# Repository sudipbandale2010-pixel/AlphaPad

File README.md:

# AlphaPad
It is a unique Macropad with unique features, it includes 9 keys and an Oled screen.

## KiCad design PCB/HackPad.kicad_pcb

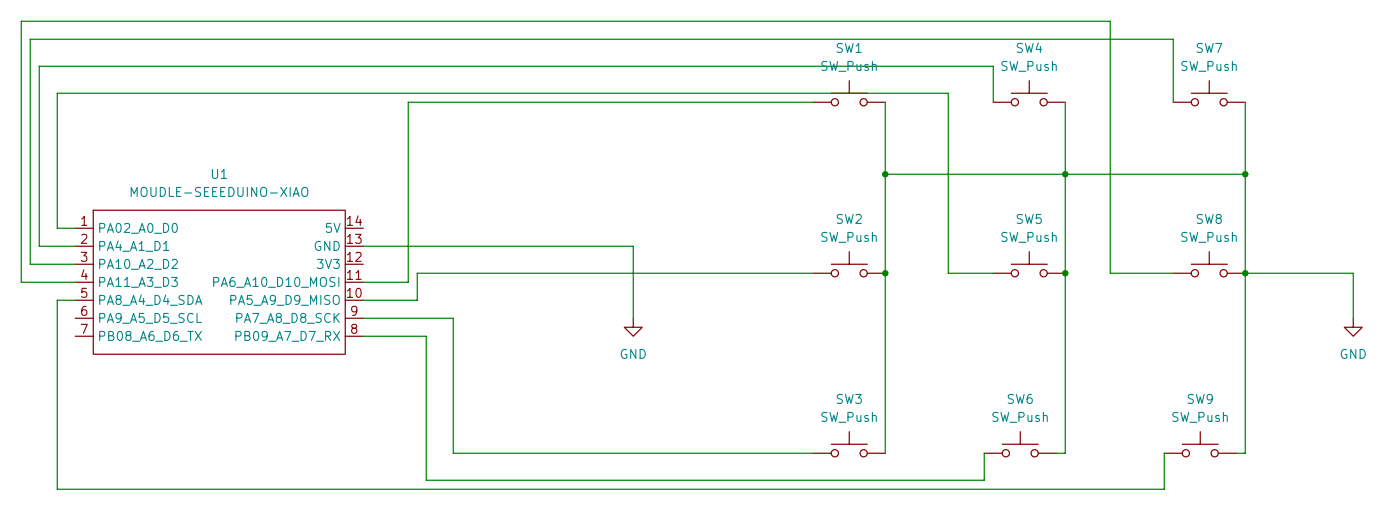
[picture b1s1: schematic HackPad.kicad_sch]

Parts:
SW1, SW2, SW3, SW4, SW5, SW6, SW7, SW8, SW9: SW_Push; SW_Cherry_MX_1.00u_PCB
U1: MOUDLE-SEEEDUINO-XIAO; XIAO-Generic-Hybrid-14P-2.54-21X17.8MM

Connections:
GND: SW1.2, SW2.2, SW3.2, SW4.2, SW5.2, SW6.2, SW7.2, SW8.2, SW9.2, U1.13 (GND)
unnamed: SW5.1, U1.1 (PA02_A0_D0)
unnamed: SW4.1, U1.2 (PA4_A1_D1)
unnamed: SW2.1, U1.10 (PA5_A9_D9_MISO)
unnamed: SW1.1, U1.11 (PA6_A10_D10_MOSI)
unnamed: SW3.1, U1.9 (PA7_A8_D8_SCK)
unnamed: SW9.1, U1.5 (PA8_A4_D4_SDA)
unnamed: SW7.1, U1.3 (PA10_A2_D2)
unnamed: SW8.1, U1.4 (PA11_A3_D3)
unnamed: SW6.1, U1.8 (PB09_A7_D7_RX)

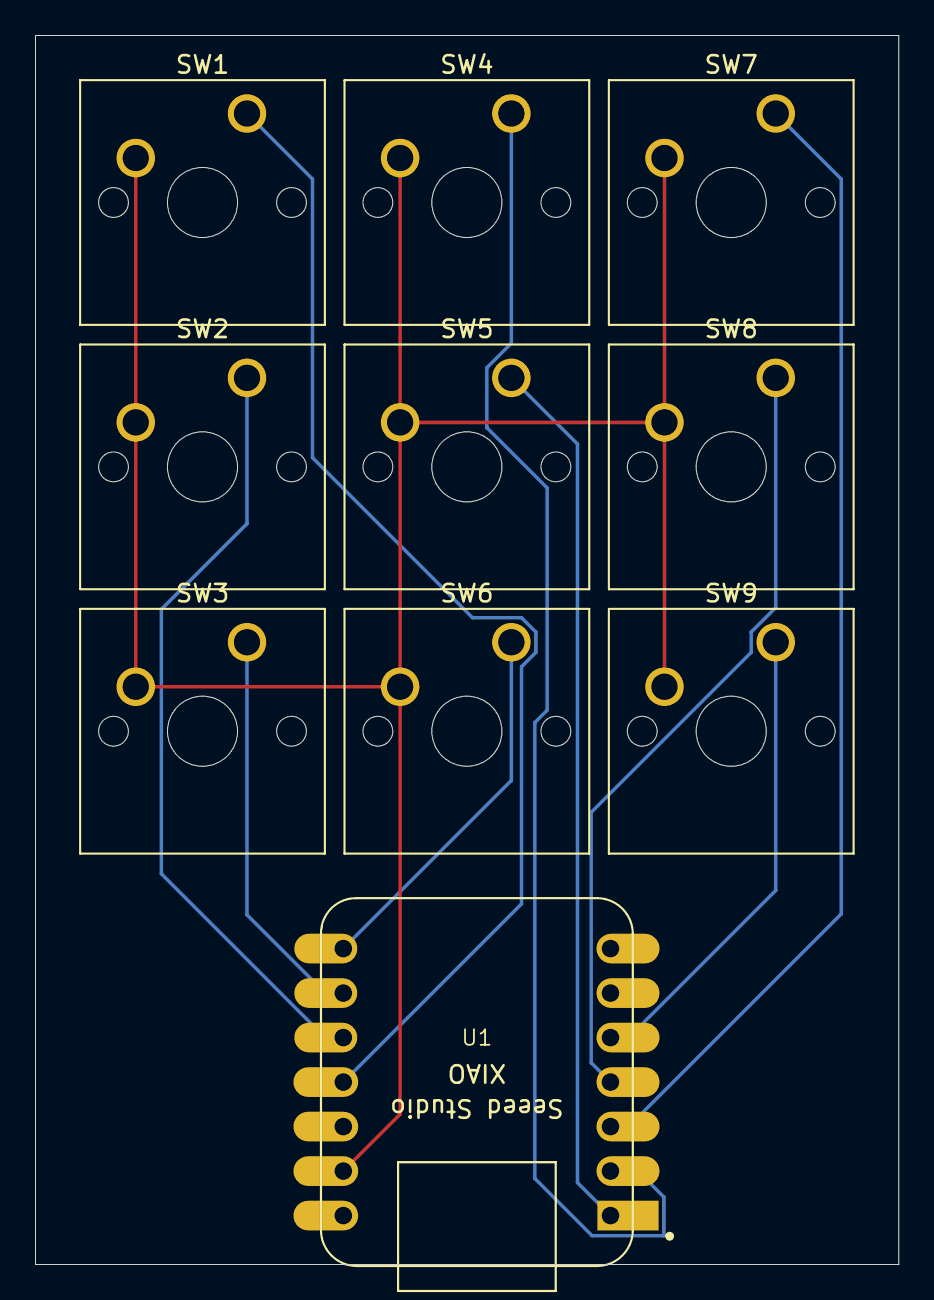
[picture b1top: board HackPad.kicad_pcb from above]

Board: 2 copper layers, 49.3 x 70.2 mm, 10 parts (0 on the bottom side), 10 nets.
